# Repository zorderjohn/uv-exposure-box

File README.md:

# uv-exposure-box

This is a Kicad project with the schematic and pcb design of an UV exposure box. Two of these boards have been used to make it. 

Two pdf's are available: 
- uv-exposure-B_Cu.pdf.  PCB layout ready to print. 
- uv-exposure-F_SilkS.pdf.  Component population layout. 

More details at:

http://jonatanmartinez.com/fun-projects/10-fun/23-uv-exposure-box

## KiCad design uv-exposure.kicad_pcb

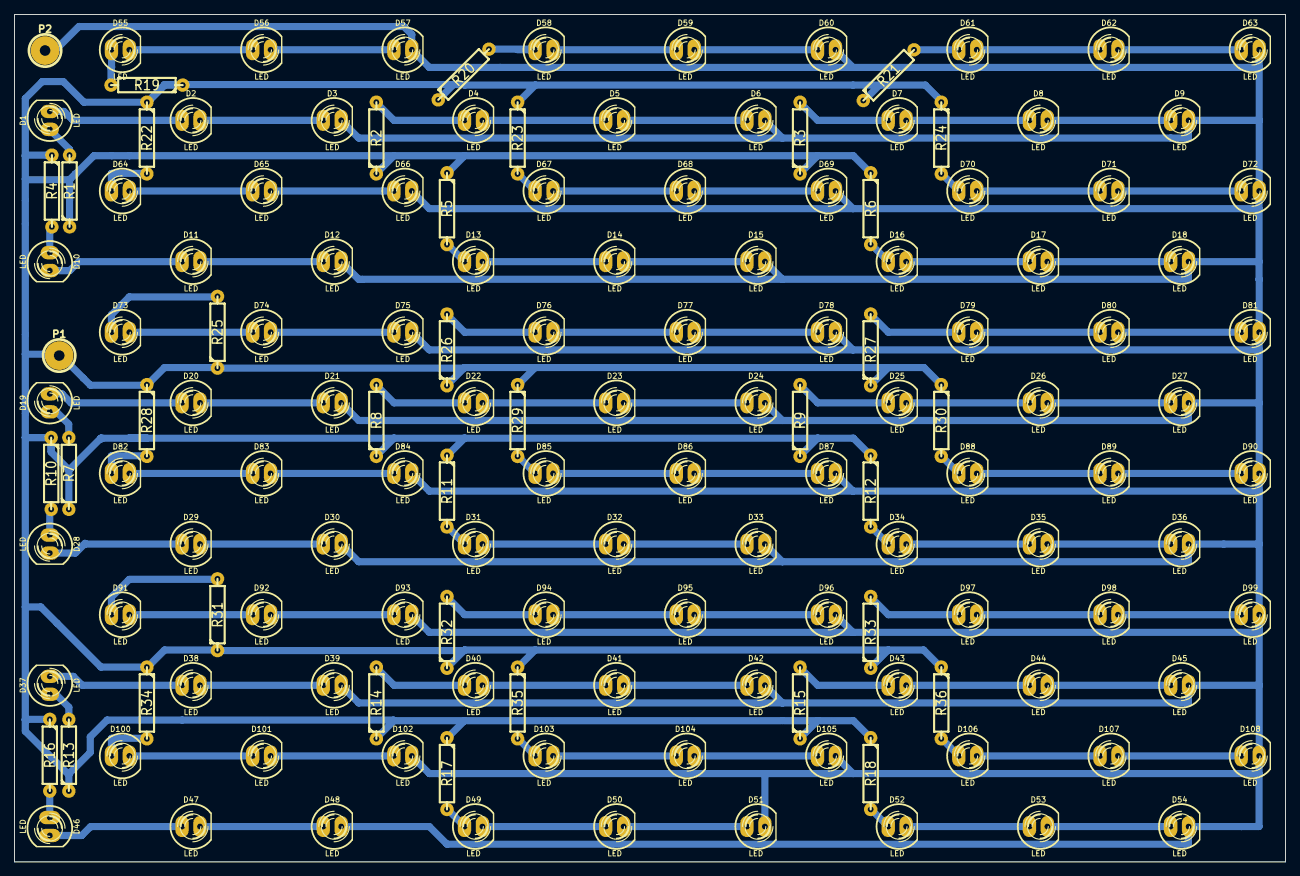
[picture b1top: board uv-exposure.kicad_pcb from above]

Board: 2 copper layers, 180.0 x 120.0 mm, 146 parts (0 on the bottom side), 110 nets.

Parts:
D1, D2, D3, D4, D5, D6, D7, D8, D9, D10, D11, D12, D13, D14, D15, D16, D17, D18, D19, D20, D21, D22, D23, D24, D25, D26, D27, D28, D29, D30, D31, D32, D33, D34, D35, D36, D37, D38, D39, D40, D41, D42, D43, D44, D45, D46, D47, D48, D49, D50, D51, D52, D53, D54, D55, D56, D57, D58, D59, D60, D61, D62, D63, D64, D65, D66, D67, D68, D69, D70, D71, D72, D73, D74, D75, D76, D77, D78, D79, D80, D81, D82, D83, D84, D85, D86, D87, D88, D89, D90, D91, D92, D93, D94, D95, D96, D97, D98, D99, D100, D101, D102, D103, D104, D105, D106, D107, D108: LED; LED-5MM
P1, P2: CONN_1; 1pin
R1, R2, R3, R4, R5, R6, R7, R8, R9, R10, R11, R12, R13, R14, R15, R16, R17, R18, R19, R20, R21, R22, R23, R24, R25, R26, R27, R28, R29, R30, R31, R32, R33, R34, R35, R36: 120; R4-LARGE_PADS

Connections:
GND: D3.2, D6.2, D9.2, D12.2, D15.2, D18.2, D21.2, D24.2, D27.2, D30.2, D33.2, D36.2, D39.2, D42.2, D45.2, D48.2, D51.2, D54.2, D57.2, D60.2, D63.2, D66.2, D69.2, D72.2, D75.2, D78.2, D81.2, D84.2, D87.2, D90.2, D93.2, D96.2, D99.2, D102.2, D105.2, D108.2, P2.1
unnamed: D1.1, R1.2
unnamed: D1.2, D2.1
unnamed: D2.2, D3.1
unnamed: D4.1, R2.2
unnamed: D4.2, D5.1
unnamed: D5.2, D6.1
unnamed: D7.1, R3.2
unnamed: D7.2, D8.1
unnamed: D8.2, D9.1
unnamed: D10.1, R4.2
unnamed: D10.2, D11.1
unnamed: D11.2, D12.1
unnamed: D13.1, R5.2
unnamed: D13.2, D14.1
unnamed: D14.2, D15.1
unnamed: D16.1, R6.2
unnamed: D16.2, D17.1
unnamed: D17.2, D18.1
unnamed: D19.1, R7.2
unnamed: D19.2, D20.1
unnamed: D20.2, D21.1
unnamed: D22.1, R8.2
unnamed: D22.2, D23.1
unnamed: D23.2, D24.1
unnamed: D25.1, R9.2
unnamed: D25.2, D26.1
unnamed: D26.2, D27.1
unnamed: D28.1, R10.2
unnamed: D28.2, D29.1
unnamed: D29.2, D30.1
unnamed: D31.1, R11.2
unnamed: D31.2, D32.1
unnamed: D32.2, D33.1
unnamed: D34.1, R12.2
unnamed: D34.2, D35.1
unnamed: D35.2, D36.1
unnamed: D37.1, R13.2
unnamed: D37.2, D38.1
unnamed: D38.2, D39.1
unnamed: D40.1, R14.2
unnamed: D40.2, D41.1
unnamed: D41.2, D42.1
unnamed: D43.1, R15.2
unnamed: D43.2, D44.1
unnamed: D44.2, D45.1
unnamed: D46.1, R16.2
unnamed: D46.2, D47.1
unnamed: D47.2, D48.1
unnamed: D49.1, R17.2
unnamed: D49.2, D50.1
unnamed: D50.2, D51.1
unnamed: D52.1, R18.2
unnamed: D52.2, D53.1
unnamed: D53.2, D54.1
unnamed: D55.1, R19.2
unnamed: D55.2, D56.1
unnamed: D56.2, D57.1
unnamed: D58.1, R20.2
unnamed: D58.2, D59.1
unnamed: D59.2, D60.1
unnamed: D61.1, R21.2
unnamed: D61.2, D62.1
unnamed: D62.2, D63.1
unnamed: D64.1, R22.2
unnamed: D64.2, D65.1
unnamed: D65.2, D66.1
unnamed: D67.1, R23.2
unnamed: D67.2, D68.1
unnamed: D68.2, D69.1
unnamed: D70.1, R24.2
unnamed: D70.2, D71.1
unnamed: D71.2, D72.1
unnamed: D73.1, R25.2
unnamed: D73.2, D74.1
unnamed: D74.2, D75.1
unnamed: D76.1, R26.2
unnamed: D76.2, D77.1
unnamed: D77.2, D78.1
unnamed: D79.1, R27.2
unnamed: D79.2, D80.1
unnamed: D80.2, D81.1
unnamed: D82.1, R28.2
unnamed: D82.2, D83.1
unnamed: D83.2, D84.1
unnamed: D85.1, R29.2
unnamed: D85.2, D86.1
unnamed: D86.2, D87.1
unnamed: D88.1, R30.2
unnamed: D88.2, D89.1
unnamed: D89.2, D90.1
unnamed: D91.1, R31.2
unnamed: D91.2, D92.1
unnamed: D92.2, D93.1
unnamed: D94.1, R32.2
unnamed: D94.2, D95.1
unnamed: D95.2, D96.1
unnamed: D97.1, R33.2
unnamed: D97.2, D98.1
unnamed: D98.2, D99.1
unnamed: D100.1, R34.2
unnamed: D100.2, D101.1
unnamed: D101.2, D102.1
unnamed: D103.1, R35.2
unnamed: D103.2, D104.1
unnamed: D104.2, D105.1
unnamed: D106.1, R36.2
unnamed: D106.2, D107.1
unnamed: D107.2, D108.1
VCC: P1.1, R1.1, R2.1, R3.1, R4.1, R5.1, R6.1, R7.1, R8.1, R9.1, R10.1, R11.1, R12.1, R13.1, R14.1, R15.1, R16.1, R17.1, R18.1, R19.1, R20.1, R21.1, R22.1, R23.1, R24.1, R25.1, R26.1, R27.1, R28.1, R29.1, R30.1, R31.1, R32.1, R33.1, R34.1, R35.1, R36.1

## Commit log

2015-04-20 Initial version. Two different circuits.
2015-04-20 All the leds now belong to the same subnet.
2015-04-20 Readme update.
2015-04-20 Readme updated.
